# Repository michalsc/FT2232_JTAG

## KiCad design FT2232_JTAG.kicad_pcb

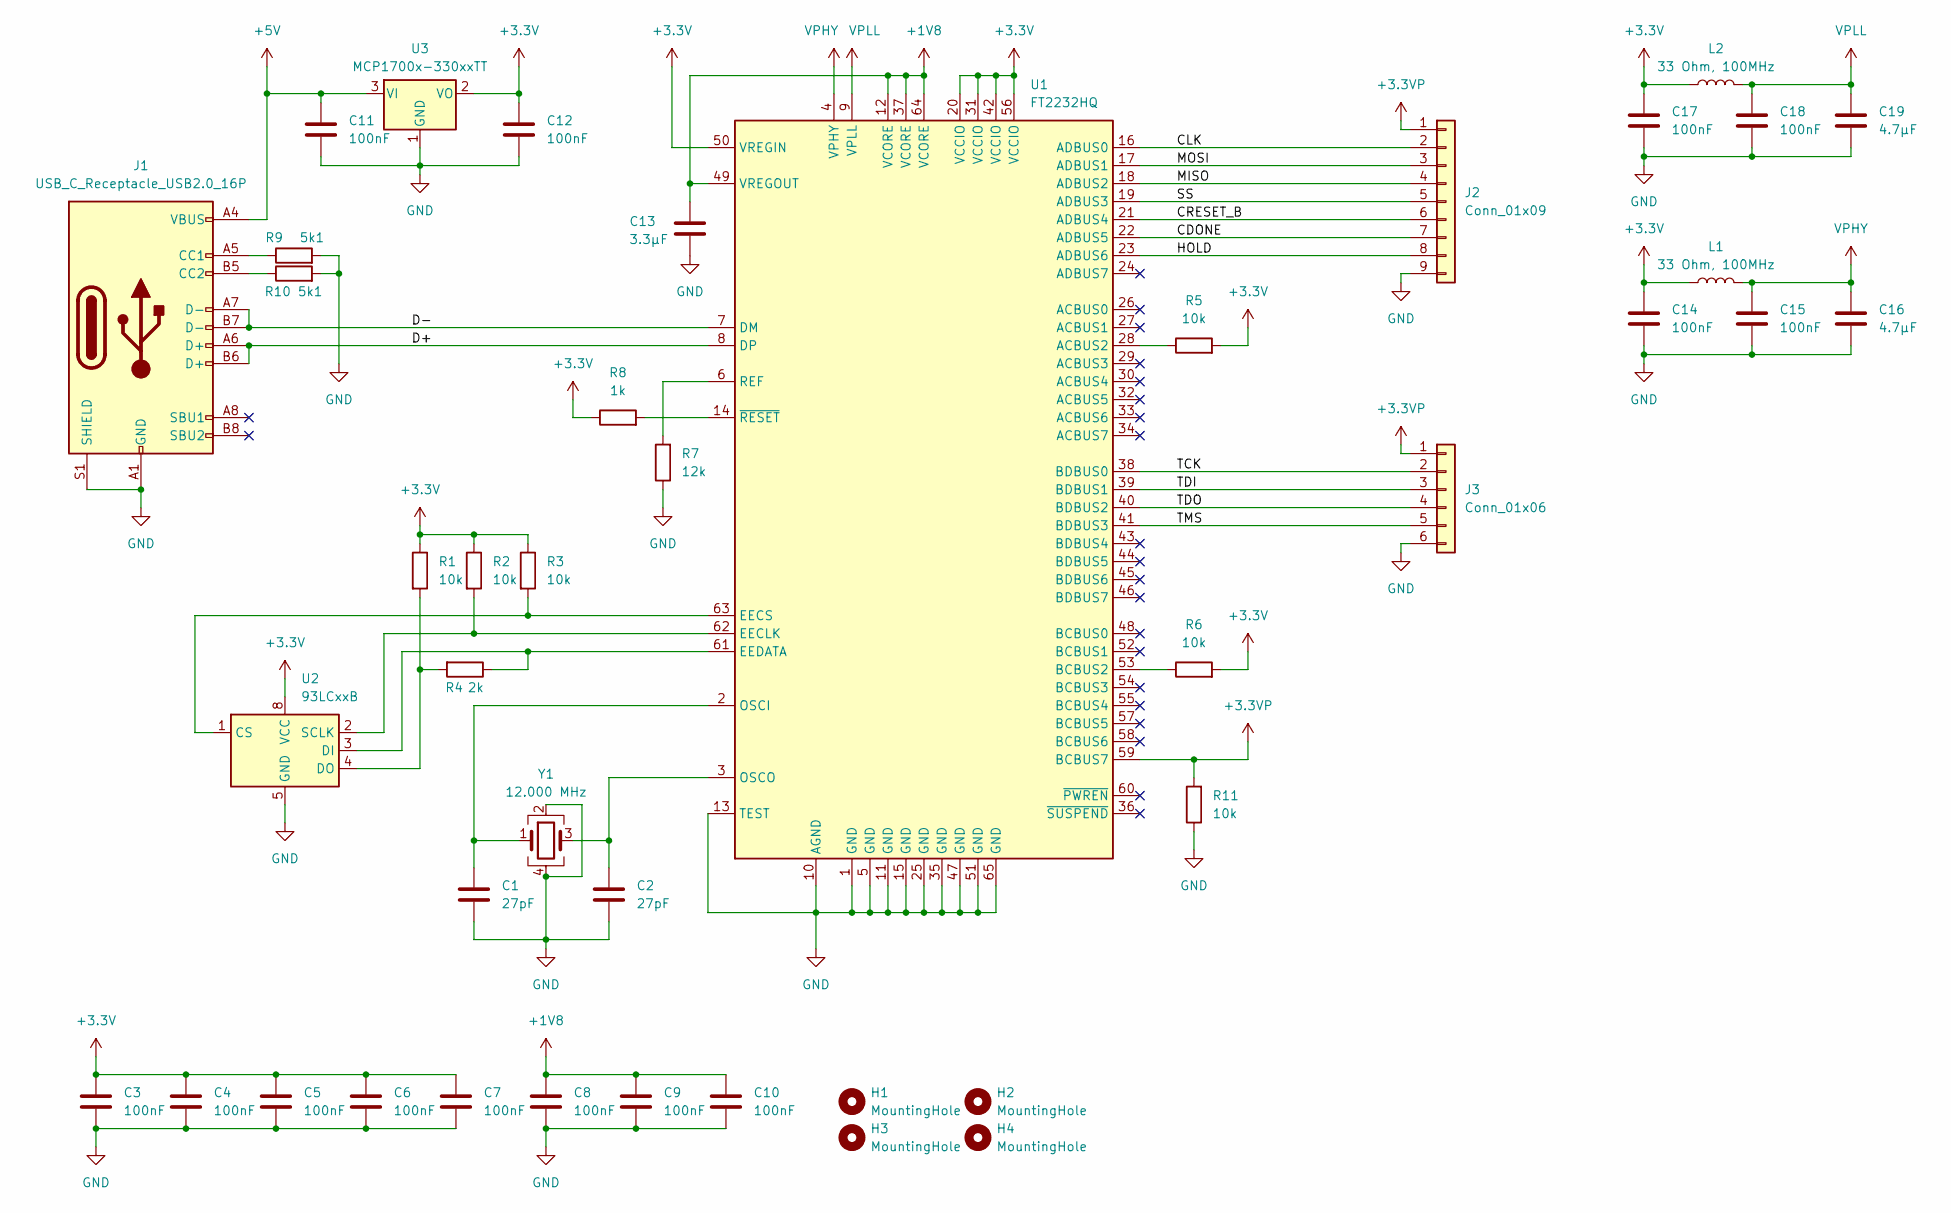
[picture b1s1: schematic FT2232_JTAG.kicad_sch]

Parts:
C1, C2: 27pF; C_0402_1005Metric; LCSC Part C1557
C3, C4, C5, C6, C7, C8, C9, C10, C11, C12, C14, C15, C17, C18: 100nF; C_0402_1005Metric; LCSC Part C3012376
C13: 3.3µF; C_0402_1005Metric; LCSC Part C695126
C16, C19: 4.7µF; C_0402_1005Metric; LCSC Part C76995
H1, H2, H3, H4: MountingHole; MountingHole_2.2mm_M2_ISO14580
J1: USB_C_Receptacle_USB2.0_16P; USB_C_Receptacle_GCT_USB4110; LCSC Part C5187472
J2: Conn_01x09; PinHeader_1x09_P2.00mm_Vertical
J3: Conn_01x06; PinHeader_1x06_P2.00mm_Vertical
L1, L2: 33 Ohm, 100MHz; L_0402_1005Metric; LCSC Part C160974
R1, R2, R3, R5, R6, R11: 10k; R_0402_1005Metric; LCSC Part C25531
R4: 2k; R_0402_1005Metric; LCSC Part C25552
R7: 12k; R_0402_1005Metric; LCSC Part C25752
R8: 1k; R_0402_1005Metric; LCSC Part C102758
R9, R10: 5k1; R_0402_1005Metric; LCSC Part C25941
U1: FT2232HQ; QFN-64-1EP_9x9mm_P0.5mm_EP4.35x4.35mm; LCSC Part C193662
U2: 93LCxxB; TSSOP-8_4.4x3mm_P0.65mm; LCSC Part C616741
U3: MCP1700x-330xxTT; SOT-23; LCSC Part C5148688
Y1: 12.000 MHz; Crystal_SMD_3225-4Pin_3.2x2.5mm; LCSC Part C9002

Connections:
+1V8: C8.1, C9.1, C10.1, C13.1, U1.12 (VCORE), U1.37 (VCORE), U1.49 (VREGOUT), U1.64 (VCORE)
+3.3V: C3.1, C4.1, C5.1, C6.1, C7.1, C12.1, C14.1, C17.1, L1.1, L2.1, R1.1, R2.1, R3.1, R5.2, R6.2, R8.1, U1.20 (VCCIO), U1.31 (VCCIO), U1.42 (VCCIO), U1.50 (VREGIN), U1.56 (VCCIO), U2.8 (VCC), U3.2 (VO)
+3.3VP: J2.1, J3.1, R11.2, U1.59 (BCBUS7)
+5V: C11.1, J1.A4 (VBUS), J1.A9 (VBUS), J1.B4 (VBUS), J1.B9 (VBUS), U3.3 (VI)
/CDONE: J2.7, U1.22 (ADBUS5)
/CLK: J2.2, U1.16 (ADBUS0)
/CRESET_B: J2.6, U1.21 (ADBUS4)
/D+: J1.A6 (D+), J1.B6 (D+), U1.8 (DP)
/D-: J1.A7 (D-), J1.B7 (D-), U1.7 (DM)
/HOLD: J2.8, U1.23 (ADBUS6)
/MISO: J2.4, U1.18 (ADBUS2)
/MOSI: J2.3, U1.17 (ADBUS1)
/SS: J2.5, U1.19 (ADBUS3)
/TCK: J3.2, U1.38 (BDBUS0)
/TDI: J3.3, U1.39 (BDBUS1)
/TDO: J3.4, U1.40 (BDBUS2)
/TMS: J3.5, U1.41 (BDBUS3)
GND: C1.2, C2.2, C3.2, C4.2, C5.2, C6.2, C7.2, C8.2, C9.2, C10.2, C11.2, C12.2, C13.2, C14.2, C15.2, C16.2, C17.2, C18.2, C19.2, J1.A1 (GND), J1.A12 (GND), J1.B1 (GND), J1.B12 (GND), J1.S1 (SHIELD), J2.9, J3.6, R7.1, R9.2, R10.2, R11.1, U1.1 (GND), U1.5 (GND), U1.10 (AGND), U1.11 (GND), U1.13 (TEST), U1.15 (GND), U1.25 (GND), U1.35 (GND), U1.47 (GND), U1.51 (GND), U1.65 (GND), U2.5 (GND), U3.1 (GND), Y1.2, Y1.4
unnamed: J1.A5 (CC1), R9.1
unnamed: J1.B5 (CC2), R10.1
unnamed: R5.1, U1.28 (ACBUS2)
unnamed: R6.1, U1.53 (BCBUS2)
unnamed: R2.2, U1.62 (EECLK), U2.2 (SCLK)
unnamed: R3.2, U1.63 (EECS), U2.1 (CS)
unnamed: R4.1, U1.61 (EEDATA), U2.3 (DI)
unnamed: C1.1, U1.2 (OSCI), Y1.1
unnamed: C2.1, U1.3 (OSCO), Y1.3
unnamed: R7.2, U1.6 (REF)
unnamed: R8.2, U1.14 (~RESET)
unnamed: R1.2, R4.2, U2.4 (DO)
VPHY: C15.1, C16.1, L1.2, U1.4 (VPHY)
VPLL: C18.1, C19.1, L2.2, U1.9 (VPLL)

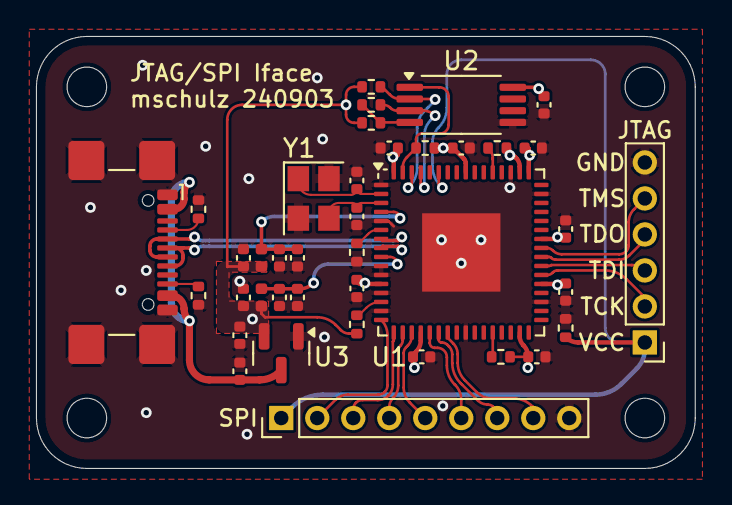
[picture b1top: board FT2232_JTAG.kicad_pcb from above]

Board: 2 copper layers, 36.6 x 24.0 mm, 43 parts (0 on the bottom side), 32 nets.

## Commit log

2024-09-03 Fixed pull on BCBUS7
2024-09-03 Routing done. DRC ToDo.
2024-09-09 added LCSC part numbers
